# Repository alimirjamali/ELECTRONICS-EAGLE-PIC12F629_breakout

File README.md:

# Microchip PIC12F629 breakout board

This is a small simple development board for 8 pin PIC micro-controllers.
I made this simple board to practice [Julian Ilett's](https://www.youtube.com/playlist?list=PLjzGSu1yGFjXSEIsOsaYfKl1xmPcji2f-) 
PIC Assembly Language Tutorials easily without requiring breadboarding or original PCB (which I did not like).
This PCB could be directly connected to & powered from PICkit 3.

## Schematic

## PCB

## Rev 1.0 PCBs

# Sample code
There is currently a simple LED dimming code in C in Hello World directory.
I will rewrite it in PIC Assembly once I learn more from Julian's Tutorial.

# License

This hardware is licensed under [Creative Commons Share Alike](http://creativecommons.org/licenses/by-sa/4.0/).

Sample Hello World C code is licensed under GPL v2.0

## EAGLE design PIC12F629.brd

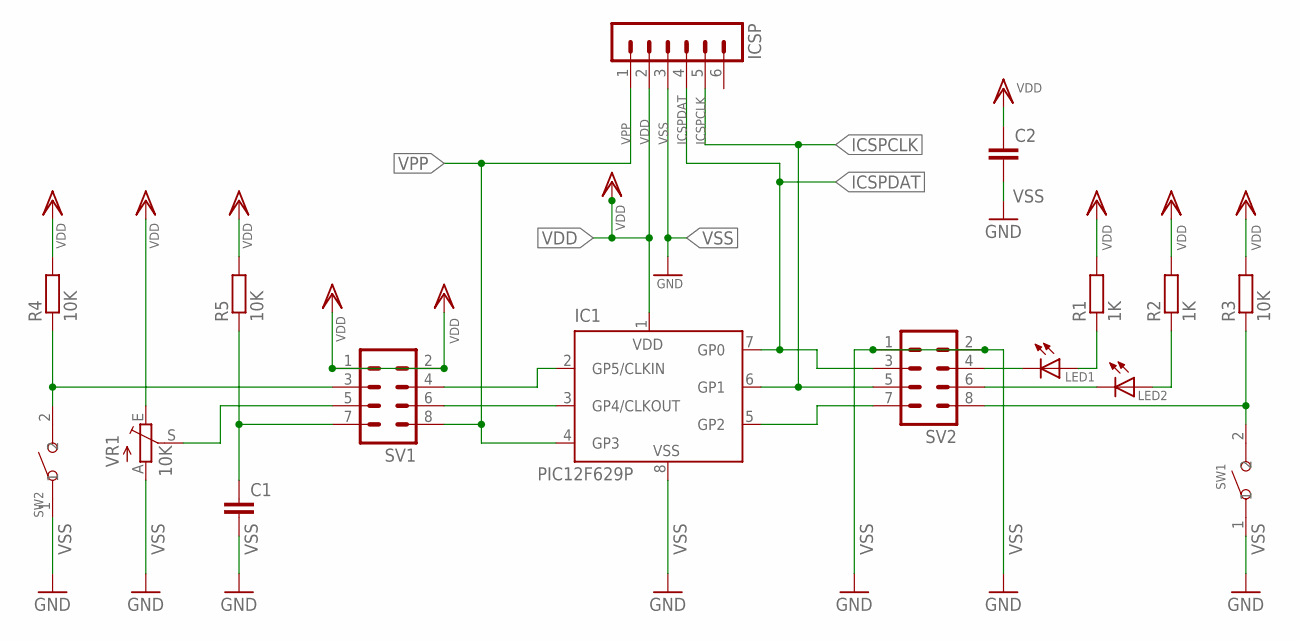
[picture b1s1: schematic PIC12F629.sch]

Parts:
C1, C2: C-EUC0805K; C0805K
IC1: PIC12F629P; DIL8
ICSP: MA06-1
LED1, LED2: LEDCHIP-LED0805; CHIP-LED0805
R1, R2: 1K; R0805
R3, R4, R5: 10K; R0805
SV1, SV2: MA04-2
SW1, SW2: SMD-BUTTON(2P-6.0X3.0X2.5MM)-DHT-1163S; SW2-4.0-6.0X3.0X2.5MM
VR1: 10K; CA6V

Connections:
ICSPCLK: IC1.6 (GP1), ICSP.5, SV2.5
ICSPDAT: IC1.7 (GP0), ICSP.4, SV2.3
unnamed: IC1.3 (GP4/CLKOUT), SV1.6
unnamed: IC1.5 (GP2), SV2.7
unnamed: IC1.2 (GP5/CLKIN), SV1.4
unnamed: LED1.C, SV2.4
unnamed: LED2.C, SV2.6
unnamed: LED1.A, R1.1
unnamed: LED2.A, R2.1
unnamed: R3.1, SV2.8, SW1.2
unnamed: R4.1, SV1.3, SW2.2
unnamed: SV1.5, VR1.S
unnamed: C1.1, R5.1, SV1.7
VDD: C2.1, IC1.1 (VDD), ICSP.2, R1.2, R2.2, R3.2, R4.2, R5.2, SV1.1, SV1.2, VR1.E
VPP: IC1.4 (GP3), ICSP.1, SV1.8
VSS: C1.2, C2.2, IC1.8 (VSS), ICSP.3, SV2.1, SV2.2, SW1.1, SW2.1, VR1.A

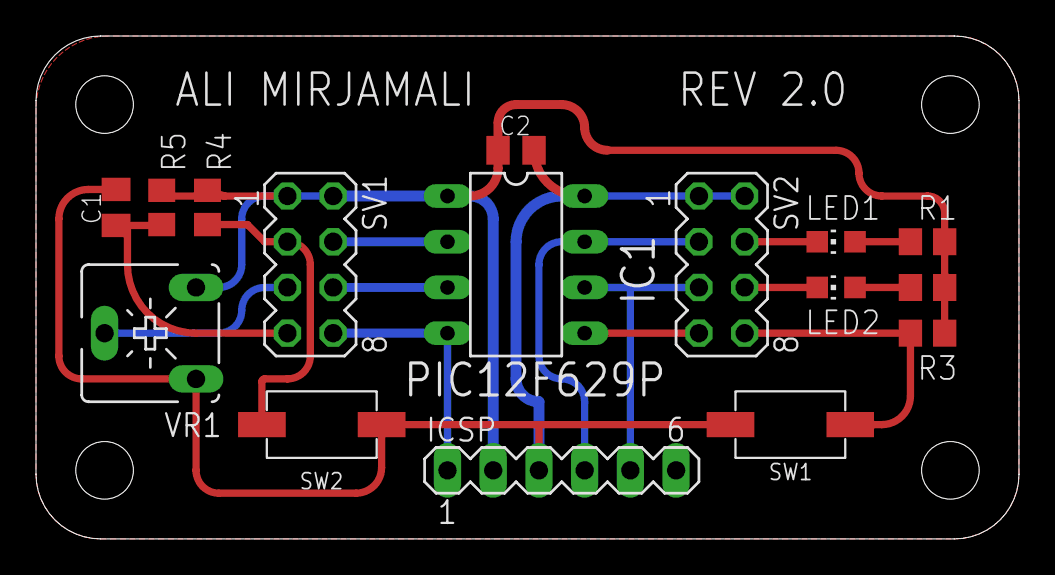
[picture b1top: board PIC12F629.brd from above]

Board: 2 copper layers, 54.6 x 27.9 mm, 16 parts (0 on the bottom side), 16 nets.

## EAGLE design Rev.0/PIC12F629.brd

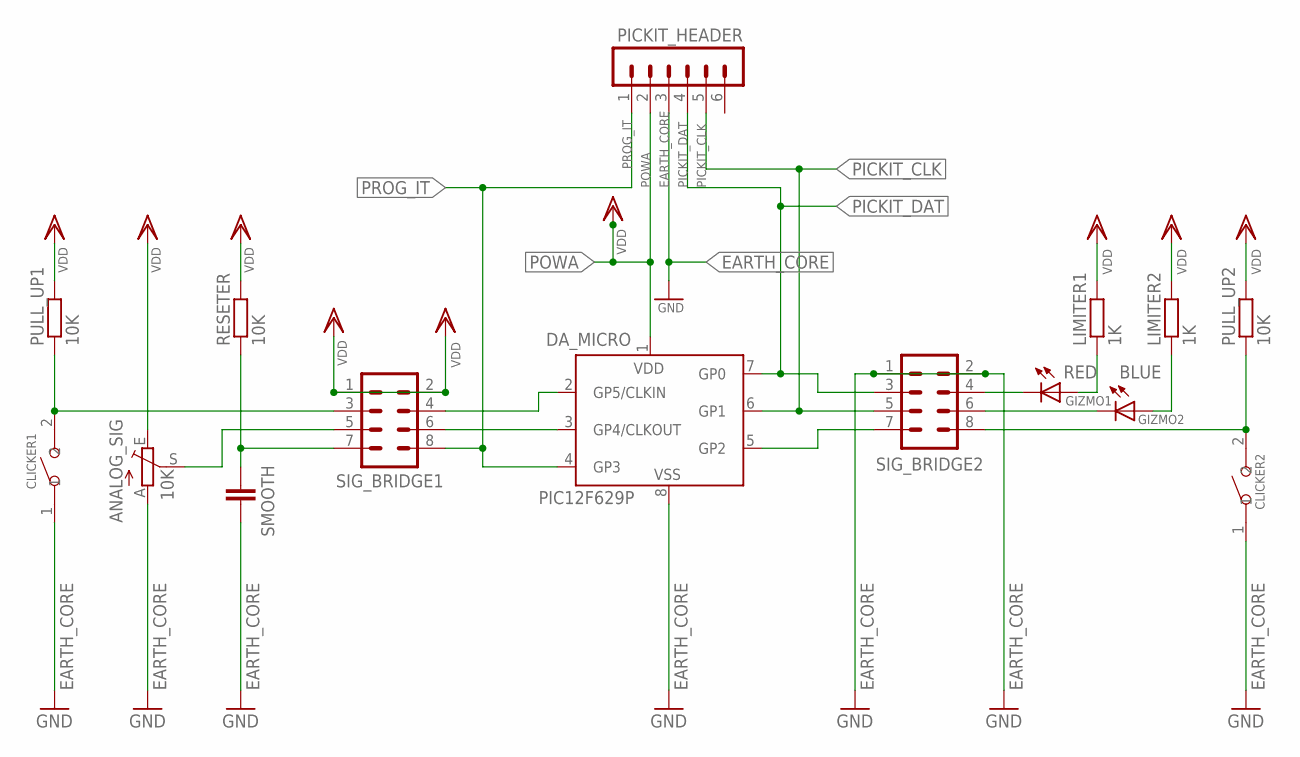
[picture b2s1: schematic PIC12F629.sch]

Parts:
ANALOG_SIG: 10K; CA6V
CLICKER1, CLICKER2: SMD-BUTTON(2P-6.0X3.0X2.5MM)-DHT-1163S; SW2-4.0-6.0X3.0X2.5MM
DA_MICRO: PIC12F629P; DIL8
GIZMO1: RED; CHIP-LED0805
GIZMO2: BLUE; CHIP-LED0805
LIMITER1, LIMITER2: 1K; R0805
PICKIT_HEADER: MA06-1
PULL_UP1, PULL_UP2: 10K; R0805
RESETER: 10K; R0805
SIG_BRIDGE1, SIG_BRIDGE2: MA04-2
SMOOTH: C-EUC0805K; C0805K

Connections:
EARTH_CORE: ANALOG_SIG.A, CLICKER1.1, CLICKER2.1, DA_MICRO.8 (VSS), PICKIT_HEADER.3, SIG_BRIDGE2.1, SIG_BRIDGE2.2, SMOOTH.2
unnamed: DA_MICRO.3 (GP4/CLKOUT), SIG_BRIDGE1.6
unnamed: DA_MICRO.5 (GP2), SIG_BRIDGE2.7
unnamed: DA_MICRO.2 (GP5/CLKIN), SIG_BRIDGE1.4
unnamed: GIZMO1.C, SIG_BRIDGE2.4
unnamed: GIZMO2.C, SIG_BRIDGE2.6
unnamed: GIZMO1.A, LIMITER1.1
unnamed: GIZMO2.A, LIMITER2.1
unnamed: CLICKER2.2, PULL_UP2.1, SIG_BRIDGE2.8
unnamed: CLICKER1.2, PULL_UP1.1, SIG_BRIDGE1.3
unnamed: ANALOG_SIG.S, SIG_BRIDGE1.5
unnamed: RESETER.1, SIG_BRIDGE1.7, SMOOTH.1
PICKIT_CLK: DA_MICRO.6 (GP1), PICKIT_HEADER.5, SIG_BRIDGE2.5
PICKIT_DAT: DA_MICRO.7 (GP0), PICKIT_HEADER.4, SIG_BRIDGE2.3
POWA: ANALOG_SIG.E, DA_MICRO.1 (VDD), LIMITER1.2, LIMITER2.2, PICKIT_HEADER.2, PULL_UP1.2, PULL_UP2.2, RESETER.2, SIG_BRIDGE1.1, SIG_BRIDGE1.2
PROG_IT: DA_MICRO.4 (GP3), PICKIT_HEADER.1, SIG_BRIDGE1.8

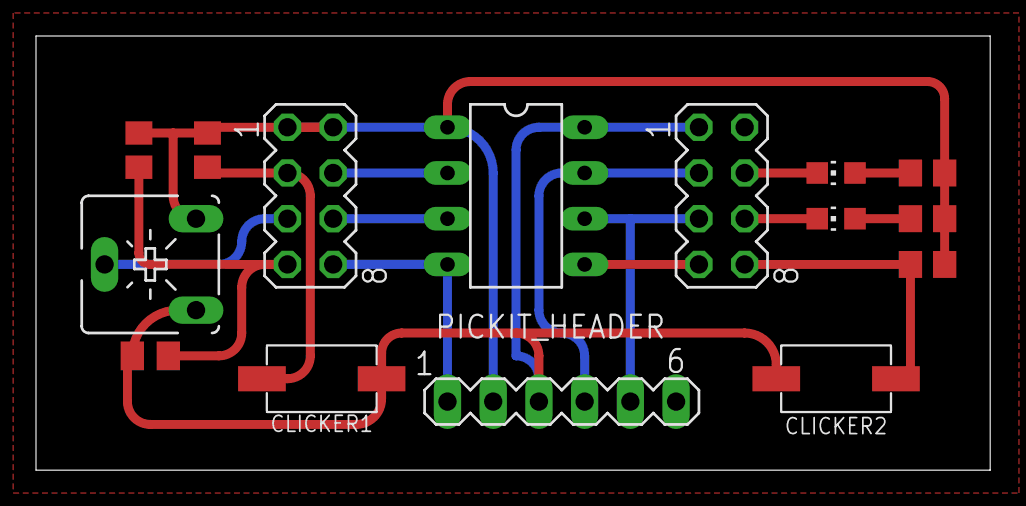
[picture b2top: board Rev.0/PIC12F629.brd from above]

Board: 2 copper layers, 53.0 x 24.1 mm, 15 parts (0 on the bottom side), 16 nets.

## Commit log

2017-03-02 Initial commit (Hardware Rev. 2)
2017-03-07 Rounded corners
